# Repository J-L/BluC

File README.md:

BluC
====

BluC

BluC is a project to mate a microcontrollers IO capabilities with the power of your smartphone

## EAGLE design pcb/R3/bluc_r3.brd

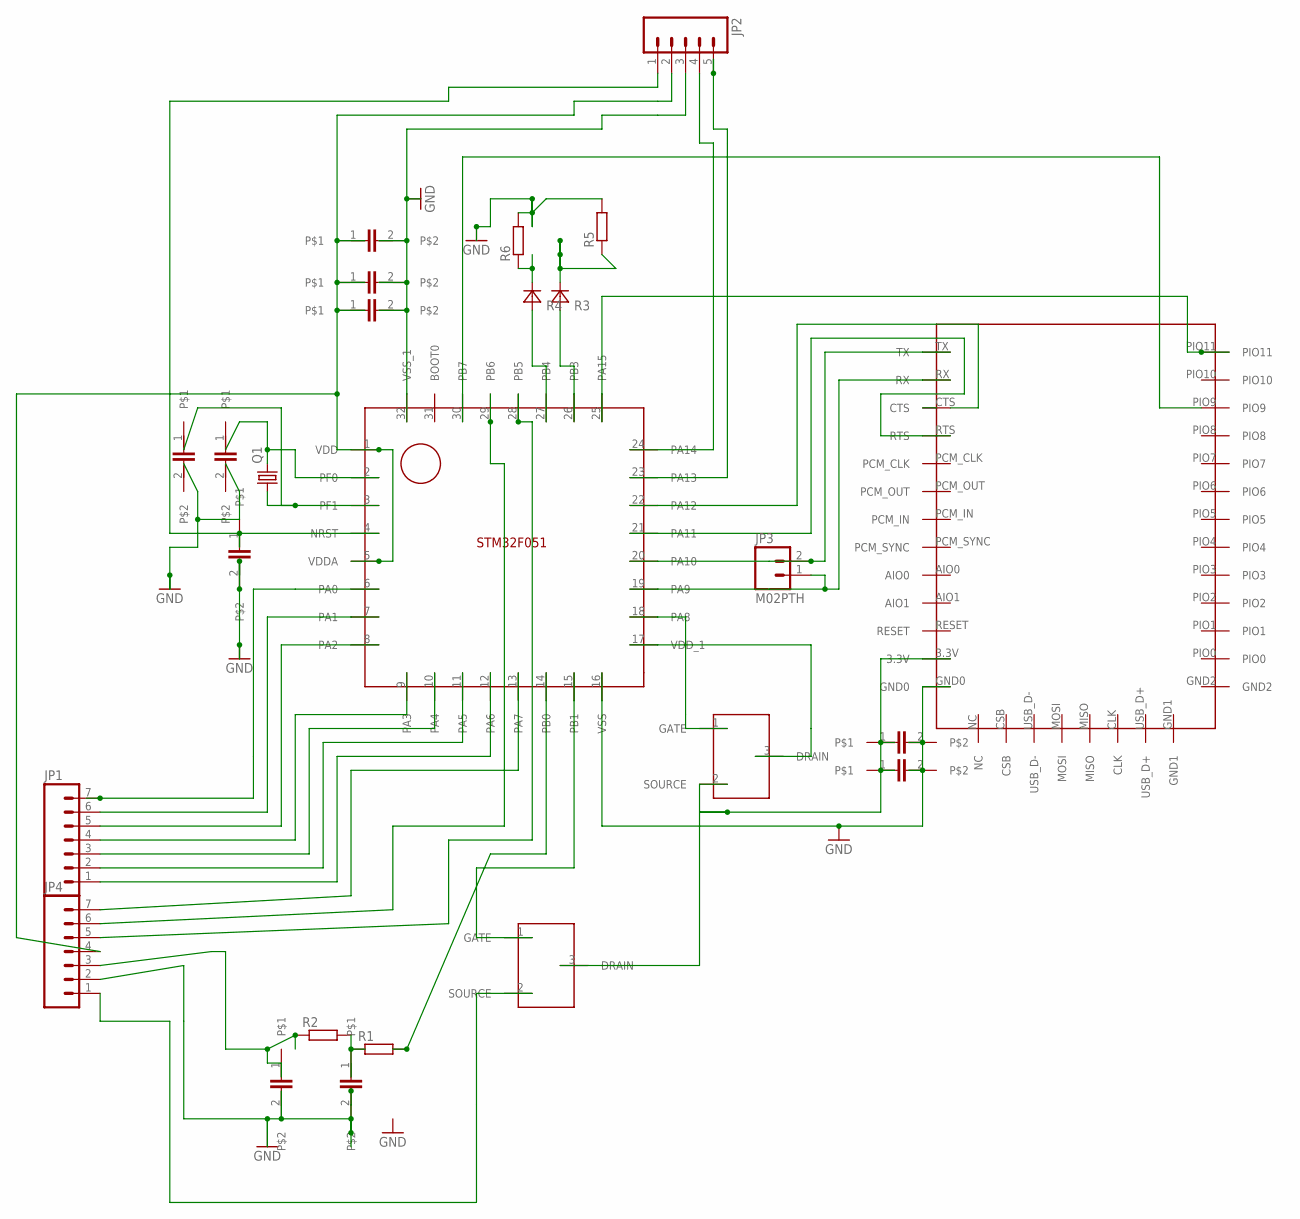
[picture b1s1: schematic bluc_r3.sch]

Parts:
JP1, JP4: M07; 1X07
JP2: M05PTH; 1X05
JP3: M02PTH; 1X02
Q1: CRYSTAL; 32768_CRYSTAL_PACKAGE
R1, R2, R5, R6: R-EU_R0603; R0603
R3, R4: DIODE; C0805K
U$1: STM32F051; LQFP32-7X7
U$2: HC-05
U$3, U$4: 2N7002K; SOT23
U$5, U$6, U$7, U$8, U$9, U$10, U$13, U$14: C0.1UF; C0805K
U$11, U$12: C1UF; C0805K

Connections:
GND: JP2.3, JP4.2, R5.2, R6.2, U$1.16 (VSS), U$1.32 (VSS_1), U$2.GND0, U$5.2, U$6.2, U$7.2, U$8.2, U$9.2, U$10.2, U$11.2, U$12.2, U$13.2, U$14.2
unnamed: JP3.2, U$1.20 (PA10), U$2.TX
unnamed: JP3.1, U$1.19 (PA9), U$2.RX
unnamed: U$1.21 (PA11), U$2.RTS
unnamed: U$1.22 (PA12), U$2.CTS
unnamed: U$1.25 (PA15), U$2.PIO11
unnamed: U$1.18 (PA8), U$3.1 (GATE)
unnamed: U$1.17 (VDD_1), U$3.3 (DRAIN)
unnamed: JP1.7, U$1.6 (PA0)
unnamed: U$2.3.3V, U$3.2 (SOURCE), U$4.3 (DRAIN), U$5.1, U$6.1
unnamed: JP2.5, U$1.23 (PA13)
unnamed: JP2.4, U$1.24 (PA14)
unnamed: JP2.1, U$1.4 (NRST), U$10.1
unnamed: JP1.6, U$1.7 (PA1)
unnamed: JP2.2, JP4.4, U$1.1 (VDD), U$1.5 (VDDA), U$7.1, U$8.1, U$9.1
unnamed: JP1.5, U$1.8 (PA2)
unnamed: U$1.15 (PB1), U$4.1 (GATE)
unnamed: R1.1, R2.2, U$11.1
unnamed: JP1.4, U$1.9 (PA3)
unnamed: R1.2, U$1.14 (PB0)
unnamed: JP4.3, R2.1, U$12.1
unnamed: JP1.3, U$1.10 (PA4)
unnamed: JP1.2, U$1.11 (PA5)
unnamed: JP1.1, U$1.12 (PA6)
unnamed: JP4.7, U$1.13 (PA7)
unnamed: JP4.1, U$4.2 (SOURCE)
unnamed: R4.1 (A), R6.1
unnamed: JP4.5, U$1.28 (PB5)
unnamed: JP4.6, U$1.29 (PB6)
unnamed: Q1.1, U$1.3 (PF1), U$14.1
unnamed: Q1.4 (2), U$1.2 (PF0), U$13.1
unnamed: R4.2 (C), U$1.27 (PB4)
unnamed: R3.2 (C), U$1.26 (PB3)
unnamed: R3.1 (A), R5.1
unnamed: U$1.30 (PB7), U$2.PIO9

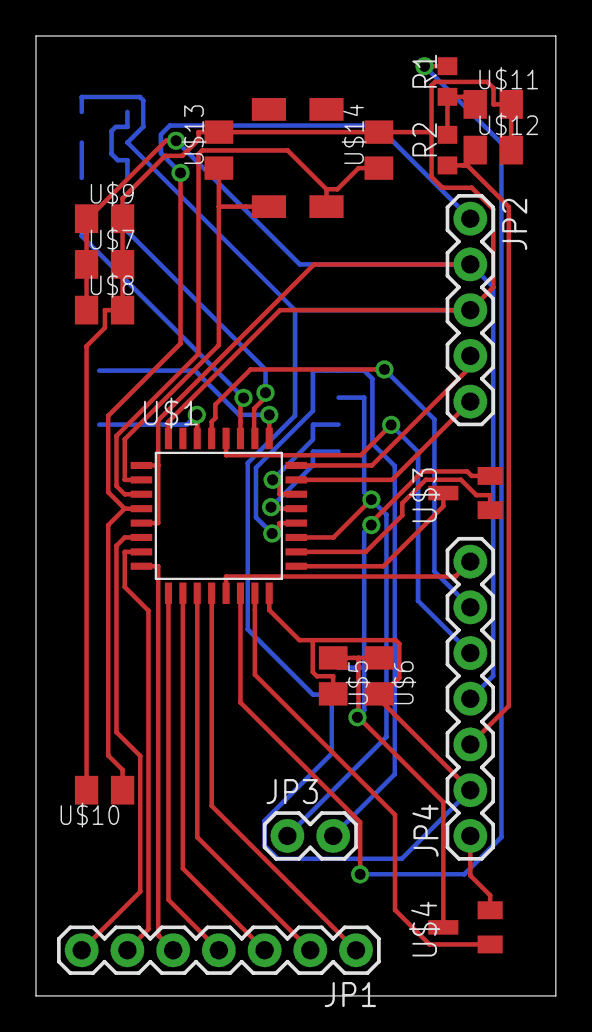
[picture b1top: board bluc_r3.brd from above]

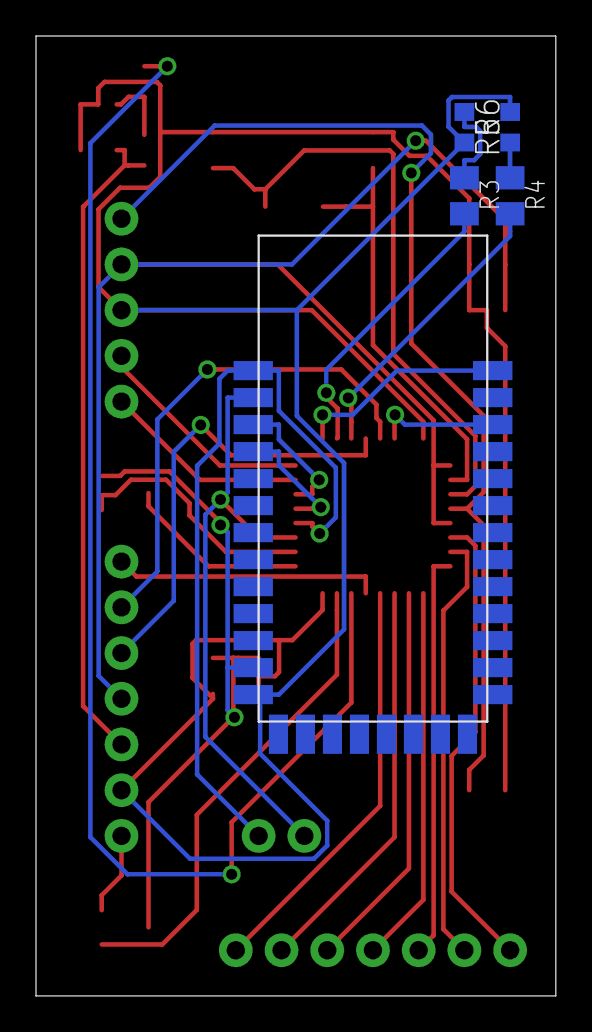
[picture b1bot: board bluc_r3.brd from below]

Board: 2 copper layers, 28.9 x 53.3 mm, 25 parts (5 on the bottom side), 35 nets.

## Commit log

2014-02-28 First commit of BluC
2014-03-01 This commit is to add all the files from the demo
2014-03-01 Include bluetooth function defintions, structures and such to follow
2014-03-01 sketching out cmd header`
2014-03-01 This is the first commit with a basic shell working- basically only a hello world for chibios.... pathetic, but we'll get there
2014-03-02 added some prototype command
2014-03-03 Directory structure added, now incuding PCB files
2014-03-05 adc not working but eh?
2014-03-06 ADC callback functioning, still need o figure out how to transwer data back and forth
2014-03-06 Added declarations for a number of functions
2014-03-07 changes include protetypes for functions, some other jazz like man texts... not sure if it still runs...
2014-03-10 ADC config changed by command, need to change while1 wait to chthread wait and push a message between them.
2014-03-14 lots of errors for sure, sketching or adc command parsing and more
2014-03-17 changing the callback to raise a semaphor, continuous mode does not work
2014-03-19 I addeded cmdadc.c, hardware c, destroyed some stuff accidentallyy:w `
2014-03-19 added structure for pin mapping some more stuffsss:
2014-03-21 bluenrg schematic
2014-03-27 accepted the fact that hc05 is going to be bt target as bt4.0 has a lower throughput, more involved
2014-04-13 reorganisation, focus on adc proper messaging. currrently threads do not exit correctly
2014-04-15 adc fixed- looks ike it is currently working, codedoes not compile, middle way through completing IO command `
2014-04-19 Overhaul, better encapsulation
2014-04-20 changed pin parsing to allow for binary and hex representations
2014-04-22 adc working
2014-04-22 adds default -0 into adc command, seems to work
2014-04-23 input mostly working for no secondary arguments, will read pins, need to allow for cts and otherwise
2014-04-24 nput works, one shot only right now, but works
2014-04-24 output possibly complete, no way to check though, no multimeterssss
2014-04-26 garbage
2014-04-26 moving about
2014-04-27 :garbage
2014-04-27 ughhhhh , i didnt know howto revert
2014-04-27 started writing uart stuff
2014-04-27 cmdUart setup now works as desired, still need to setup the backend for the uart backend, will create new branch to do so
2014-04-28 serial now can kill off shell thread, will need to work on restarting it
2014-04-29 output fix, looks right for now
2014-04-30 nothing really, want to switch branches to pwm
2014-04-30 merging uartstart
2014-05-03 pwm not done, ecided to port to stm32L1 now:q

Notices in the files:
parts and their libraries:
SparkFun-Connectors: Licensing: Creative Commons ShareAlike 4.0 International - https://creativecommons.org/licenses/by-sa/4.0
